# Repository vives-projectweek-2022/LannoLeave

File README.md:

# Lannooleaf

> VIVES Project Week 2022

## Project overview

<!-- bijwerken -->

* Connectable 3D-printed leaves
* PCB-design with LEDs & communications
* Use an OTS or own communication protocol
* Webpage
* Control of leds

## [Hardware](./hardware)

### [Shape](./hardware/shape/)

Dit is onze shape. Een primitive unit met 8 leafs.

### [PCB](./hardware/pcb/)

<!-- afbeelding hardware -->

Iedere PCB bevat elk 16 RGB LED's en beschikken ieder over een eigen Raspberry Pi Pico en spanningsomzetter. De volledige documentatie over de hardware kan men [hier](./hardware/pcb/README.md) terugvinden.

## [Firmware](./firmware)

<!-- Joey, afbeelding Pico? -->

<!-- aanvullen -->

De firmware documentatie wordt automatisch gegenereed tijdens het build procces van de firmware. Deze is te vinden in de [firmware](./firmware/) folder waar het build procces word uitgelegd.

## [Software](./software/)

The [API](./software/api) connect with the SPI interface and communicates with the frontend, artnet and has a socket to run python processed gifs.

The [ArtNet](./software/artnet) api reicieves artnet broadcast messages ans sends them trough the websochet of the api to controll all the leds. The api mapps them depending on the coords.

The [Frontend](./software/frontend) from Jay is the webinterface and all of its files.

## Credits

### Team Members

* [Arno Schoutteten](https://github.com/madness007)
* [Jens Vanhove](https://github.com/JensVA)
* [Joey De Smet](https://github.com/JoeyDeSmet)
* [Jay D'Hulster](https://github.com/JayDHulster)

### Mentors

* [Nico De Witte](https://github.com/BioBoost)
* [Piet Cordemans](https://github.com/pcordemans)
* [Sille Van Landschoot](https://github.com/sillevl)
* [Jonas Lannoo](https://github.com/JonasLannoo)

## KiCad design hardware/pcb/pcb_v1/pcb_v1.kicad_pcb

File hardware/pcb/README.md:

# PCB Lannooleaf

## Schematic

## PCB (leaf)

| Front | Back |
|---|---|
|  |  |

## PCB (verbindingsstuk)

| Front | Back |
|---|---|
|  |  |

## Eigenschappen voedingsschakeling (LM2596)

* Bereik ingangsspanning: 4,5 - 40V (wij gebruiken 24V)
* Maximale uitgangsstroom: 3A

We hebben 16 RGB LED's die theoretisch maximaal 50mA nodig hebben. Samen met de pico die maximaal 100mA verbruikt komt dit neer op een totale stroom van `900mA` (op 5V) per leaf wat neerkomt op een `vermogen van 4,5W`. De stroom aan de 24V-kant is natuurlijk een stuk minder en bedraagt `190mA`. Het verlagen van de stroom tussen de leafs was de reden van het gebruiken van een spanningsomzetter per leaf.

## Aansluiten leafs

Om de leafs met elkaar te verbinden moeten de verbindingsstukken met hun male headers geklikt worden in de female headers van de leafs (female headers kant van Pico). Op onderstaande afbeelding kan men de functie van iedere pin zien op de leaf.

De buitenste 2 pinnen zijn voor het doorkoppelen van de voeding (24V en GND) tussen de leafs. De pinnen in het midden zijn beide dezelfde 'select' pin die dient voor het discovery-protocol. De overige pinnen dienen voor het doorkoppelen van de I²C-bus met SDA aan de binnenkant en SCL aan de buitenkant.

Let op dat je de spanning niet omgekeerd aansluit bij het eventueel rechtstreeks voeden van de leafs aan de headers omdat er `GEEN polariteitsbeveiliging` aanwezig is op deze versie van de PCB. Het is veiliger om de PCB's te voeden door gebruik te maken van de barrel-jack connector die men kan solderen op de voorziene plaats op de PCB.

## BOM (Bill of Materials)

| Designator | Quantity | Description | Footprint | Distributor | Ordercode | Price |
|---|---|---|---|---|---|---|
| U1 | 1 | Raspberry Pi Pico  | 2.54mm (2x20) | Farnell | [3643332](https://be.farnell.com/raspberry-pi/raspberry-pi-pico/raspberry-pi-32bit-arm-cortex/dp/3643332) | 3,27 € (1+) |
| | 2 | Headers pico  | 2.54mm (1x20) | TME | [ZL201-20G](https://www.tme.eu/be/nl/details/zl201-20g/lijsten-en-pin-achtige-stopcontacten/connfly/ds1021-1-20sf11/) | 0,17267  € (10+) |
| U2 | 1 | LM2575-05 (ADJ) | TO-263-5 | Farnell | [2534162](https://be.farnell.com/on-semiconductor/lm2596dsadjg/dc-dc-conv-buck-3a-150khz-to-263/dp/2534162) | 2,65 € (10+) |
| D1 - D16 | 16 | WS2812B addressable LEDS | 5050 | TME | [WS2812B-V5](https://www.tme.eu/be/nl/details/ws2812b-v5/led-diodes-smd-gekleurd/worldsemi/) | 0,1490 € (50+) |
| C1 - C16, C18, C23| 18 | 100nF | 0805 | Farnell | [2320821](https://be.farnell.com/multicomp/mc0805b104k101ct/cap-0-1-f-100v-10-x7r-0805/dp/2320821) | 0,048 € (250+) |
| C17, C22 | 2 | 1nF | 0805 | Farnell | [3019871](https://be.farnell.com/yageo/cc0805krx7r9bb102/cap-1000pf-50v-10-x7r-0805/dp/3019871) | 0,077 € (10+) |
| C19, C24 | 2 | 1µF | 0805 | Farnell | [3013482](https://be.farnell.com/samsung-electro-mechanics/cl21b105kbfnnne/cap-1uf-50v-mlcc-0805/dp/3013482) | 0,052 € (5+) |
| C20 | 1 | 100µF | 6,3x7,7mm | Farnell | [2611381](https://be.farnell.com/multicomp/mcvvt035m101ea6l/cap-100-f-35v-smd/dp/2611381) | 0,156 € (1+) |
| C21 | 1 | 220µF | 8x10,5mm | Farnell | [2611361](https://be.farnell.com/multicomp/mcvvt016m221fb3l/cap-220-f-16v-smd/dp/2611361) | 0,22 € (10+) |
| D17 | 1 | SS34 | DO-214AC (SMA) | Farnell | [2101195](https://be.farnell.com/multicomp/ss34a/diode-rectifier-3a-40v-do-214ac/dp/2101195) | 0,293 € (10+) |
| L1 | 1 | 33µH | 12x12x8mm | Farnell | [2288506](https://be.farnell.com/coilcraft/mss1278-333mld/inductor-33uh-3-1a-20-pwr-9-5mhz/dp/2288506) | 1,82 € (10+) |
| R1 | 1 | 3,1k | 0805 | Farnell | [2502845](https://be.farnell.com/walsin/wf08w3091btl/res-3k09-0-1-100v-0805-thin-film/dp/2502845) | 0,112 € (10+) |
| R2 | 1 | 1k | 0805 | Farnell | [2502859](https://be.farnell.com/walsin/wf08u1001btl/res-1k-0-1-100v-0805-thin-film/dp/2502859) | 0,103 € (10+) |
| J1-J6 | 6 | Pin sockets (2x5) | 2.54mm | TME | [ZL262-10DG](https://www.tme.eu/be/nl/details/zl262-10dg/lijsten-en-pin-achtige-stopcontacten/connfly/ds1023-2-5s21/) | 0,08281 € (100+) |

Volgende items zijn enkel voor de `controller` (leaf met speciale functionaliteit):

| Designator | Quantity | Description | Footprint | Distributor | Ordercode | Price |
|---|---|---|---|---|---|---|
| J7 | 1 | Power connector | | TME | [PC-GK2.5/SMD](https://www.tme.eu/be/en/details/pc-gk2.5_smd/dc-power-connectors/ninigi/) | 0,9084 € (2+) |
| J8 | 1 | Pin headers (1x5) right angle | 2.54mm | Farnell | [2356179](https://be.farnell.com/wurth-elektronik/61300511021/header-2-54mm-pin-tht-r-a-5way/dp/2356179) | 0,315 € (10+) |

Volgend item is enkel voor de `verbindingsstukken` tussen de leafs:

| Designator | Quantity | Description | Footprint | Distributor | Ordercode | Price |
|---|---|---|---|---|---|---|
| J1, J2 | 2 | Pin headers (2x5) | 2.54mm | TME | [ZL202-10G](https://www.tme.eu/be/nl/details/zl202-10g/lijsten-en-pin-achtige-stopcontacten/connfly/ds1021-2-5sf11-b/) | 0.05254 € (50+) |

Totale prijs componenten leaf: `12,9722 €`

Totale prijs componenten controller: `14,1956 €`

Totale prijs componenten verbindingsstuk: `0,10508 €`

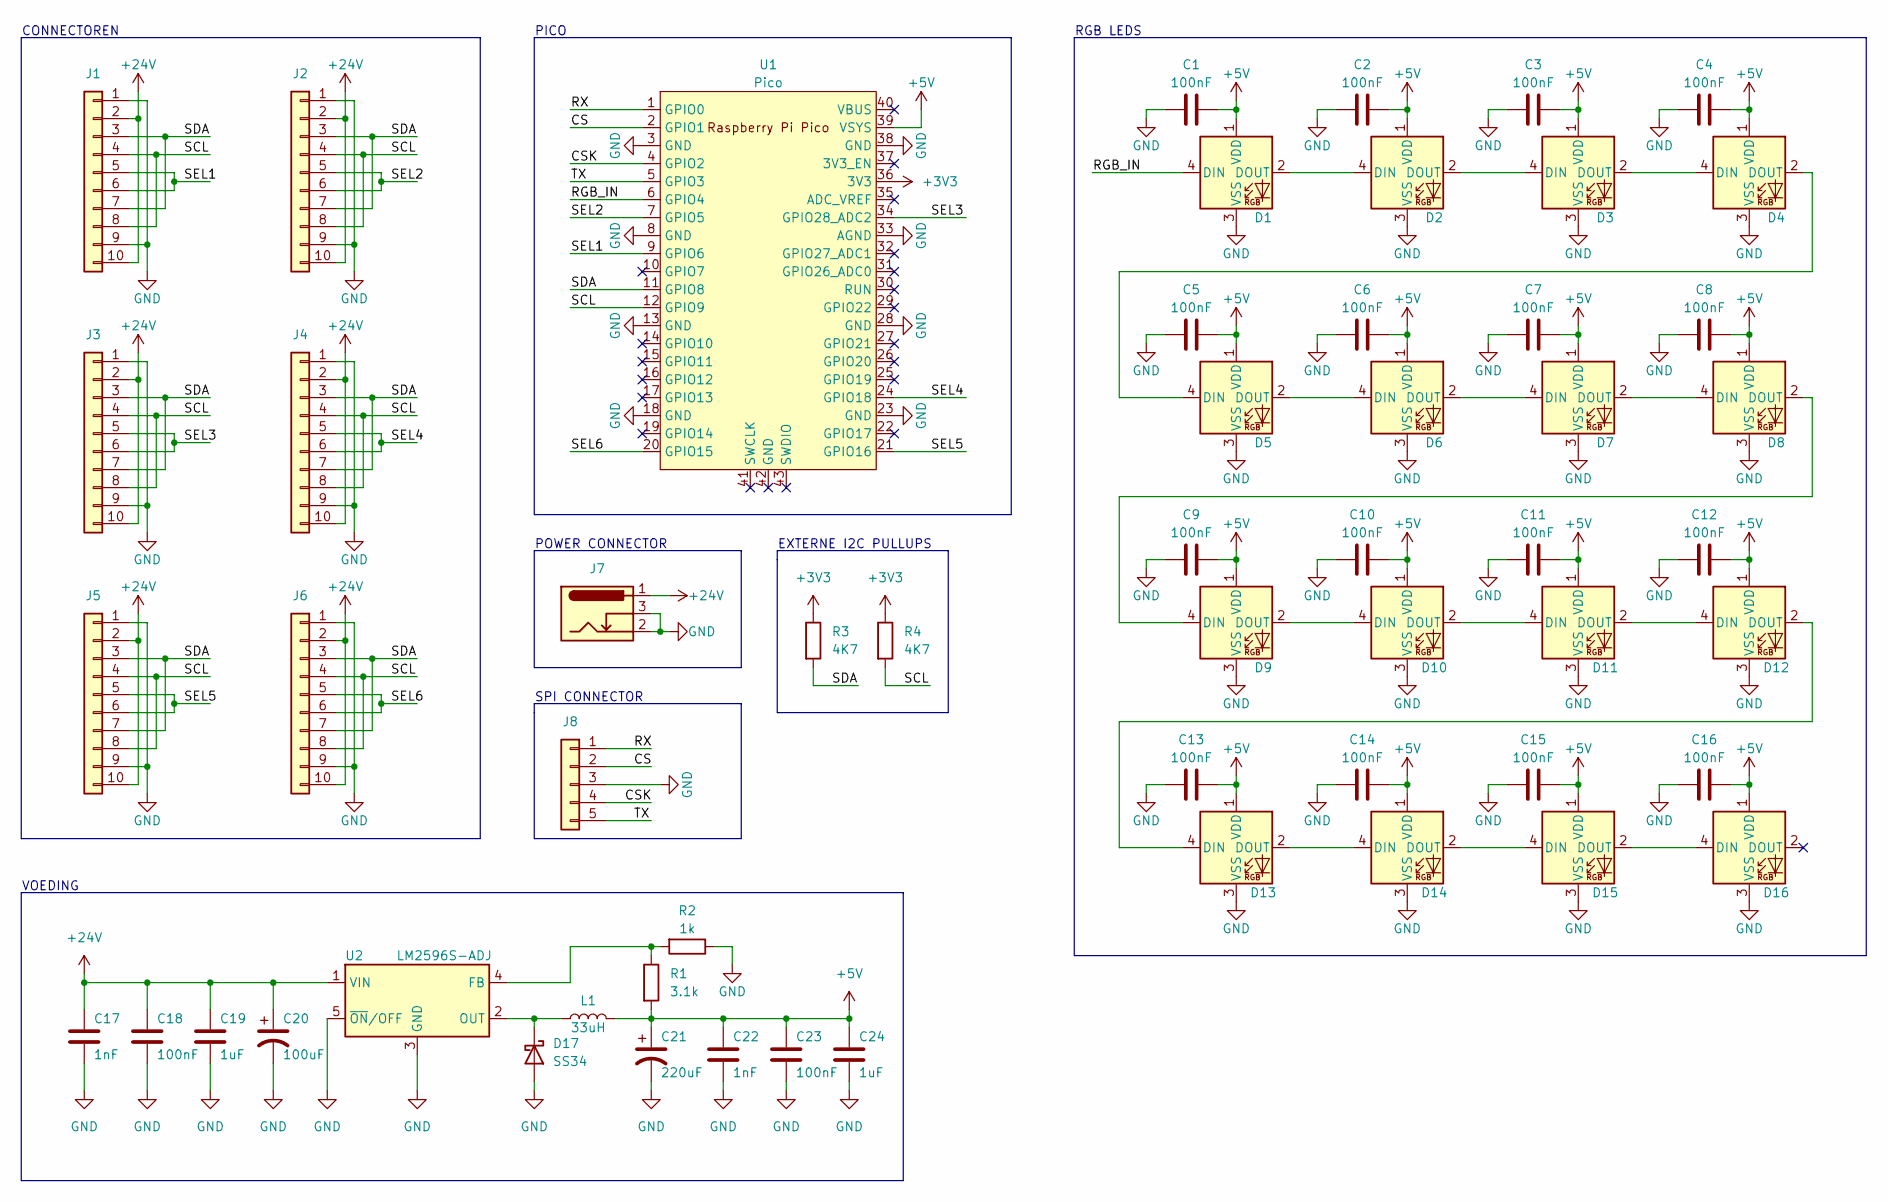
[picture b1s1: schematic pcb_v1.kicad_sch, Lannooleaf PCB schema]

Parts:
C1, C2, C3, C4, C5, C6, C7, C8, C9, C10, C11, C12, C13, C14, C15, C16, C18, C23: 100nF; C_0805_2012Metric
C17, C22: 1nF; C_0805_2012Metric
C19, C24: 1uF; C_0805_2012Metric
C20: 100uF; CP_Elec_6.3x7.7
C21: 220uF; CP_Elec_8x10.5
D1, D2, D3, D4, D5, D6, D7, D8, D9, D10, D11, D12, D13, D14, D15, D16: WS2812B; LED_WS2812B_PLCC4_5.0x5.0mm_P3.2mm
D17: SS34; D_SMA_Handsoldering
J1, J2, J3, J4, J5, J6: Conn_01x10; PinHeader_2x05_P2.54mm_Vertical
J7: Barrel_Jack_Switch; BarrelJack_CLIFF_FC681465S_SMT_Horizontal
J8: Conn_01x05; PinSocket_1x05_P2.54mm_Horizontal
L1: 33uH; L_12x12mm_H8mm
R1: 3.1k; R_0805_2012Metric
R2: 1k; R_0805_2012Metric
R3, R4: 4K7; R_0805_2012Metric
U1: Pico; RPi_Pico_SMD_TH
U2: LM2596S-ADJ; TO-263-5_TabPin3

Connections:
+3V3: R3.1, R4.1, U1.36 (3V3)
+5V: C1.2, C2.2, C3.2, C4.2, C5.2, C6.2, C7.2, C8.2, C9.2, C10.2, C11.2, C12.2, C13.2, C14.2, C15.2, C16.2, C21.1, C22.1, C23.1, C24.1, D1.1 (VDD), D2.1 (VDD), D3.1 (VDD), D4.1 (VDD), D5.1 (VDD), D6.1 (VDD), D7.1 (VDD), D8.1 (VDD), D9.1 (VDD), D10.1 (VDD), D11.1 (VDD), D12.1 (VDD), D13.1 (VDD), D14.1 (VDD), D15.1 (VDD), D16.1 (VDD), L1.2, R1.2, U1.39 (VSYS)
+24V: C17.1, C18.1, C19.1, C20.1, J1.2, J1.10, J2.2, J2.10, J3.2, J3.10, J4.2, J4.10, J5.2, J5.10, J6.2, J6.10, J7.1, U2.1 (VIN)
/CS: J8.2, U1.2 (GPIO1)
/CSK: J8.4, U1.4 (GPIO2)
/RGB_IN: D1.4 (DIN), U1.6 (GPIO4)
/RX: J8.1, U1.1 (GPIO0)
/SCL: J1.4, J1.8, J2.4, J2.8, J3.4, J3.8, J4.4, J4.8, J5.4, J5.8, J6.4, J6.8, R4.2, U1.12 (GPIO9)
/SDA: J1.3, J1.7, J2.3, J2.7, J3.3, J3.7, J4.3, J4.7, J5.3, J5.7, J6.3, J6.7, R3.2, U1.11 (GPIO8)
/SEL1: J1.5, J1.6, U1.9 (GPIO6)
/SEL2: J2.5, J2.6, U1.7 (GPIO5)
/SEL3: J3.5, J3.6, U1.34 (GPIO28_ADC2)
/SEL4: J4.5, J4.6, U1.24 (GPIO18)
/SEL5: J5.5, J5.6, U1.21 (GPIO16)
/SEL6: J6.5, J6.6, U1.20 (GPIO15)
/TX: J8.5, U1.5 (GPIO3)
GND: C1.1, C2.1, C3.1, C4.1, C5.1, C6.1, C7.1, C8.1, C9.1, C10.1, C11.1, C12.1, C13.1, C14.1, C15.1, C16.1, C17.2, C18.2, C19.2, C20.2, C21.2, C22.2, C23.2, C24.2, D1.3 (VSS), D2.3 (VSS), D3.3 (VSS), D4.3 (VSS), D5.3 (VSS), D6.3 (VSS), D7.3 (VSS), D8.3 (VSS), D9.3 (VSS), D10.3 (VSS), D11.3 (VSS), D12.3 (VSS), D13.3 (VSS), D14.3 (VSS), D15.3 (VSS), D16.3 (VSS), D17.2 (A), J1.1, J1.9, J2.1, J2.9, J3.1, J3.9, J4.1, J4.9, J5.1, J5.9, J6.1, J6.9, J7.2, J7.3, J8.3, R2.1, U1.3 (GND), U1.8 (GND), U1.13 (GND), U1.18 (GND), U1.23 (GND), U1.28 (GND), U1.33 (AGND), U1.38 (GND), U2.3 (GND), U2.5 (~ON/OFF)
unnamed: D1.2 (DOUT), D2.4 (DIN)
unnamed: D2.2 (DOUT), D3.4 (DIN)
unnamed: D3.2 (DOUT), D4.4 (DIN)
unnamed: D4.2 (DOUT), D5.4 (DIN)
unnamed: D5.2 (DOUT), D6.4 (DIN)
unnamed: D6.2 (DOUT), D7.4 (DIN)
unnamed: D7.2 (DOUT), D8.4 (DIN)
unnamed: D8.2 (DOUT), D9.4 (DIN)
unnamed: D10.2 (DOUT), D11.4 (DIN)
unnamed: D9.2 (DOUT), D10.4 (DIN)
unnamed: D11.2 (DOUT), D12.4 (DIN)
unnamed: D12.2 (DOUT), D13.4 (DIN)
unnamed: D13.2 (DOUT), D14.4 (DIN)
unnamed: D14.2 (DOUT), D15.4 (DIN)
unnamed: D15.2 (DOUT), D16.4 (DIN)
unnamed: D17.1 (K), L1.1, U2.2 (OUT)
unnamed: R1.1, R2.2, U2.4 (FB)

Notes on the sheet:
POWER CONNECTOR
EXTERNE I2C PULLUPS
VOEDING
PICO
CONNECTOREN
SPI CONNECTOR
RGB LEDS

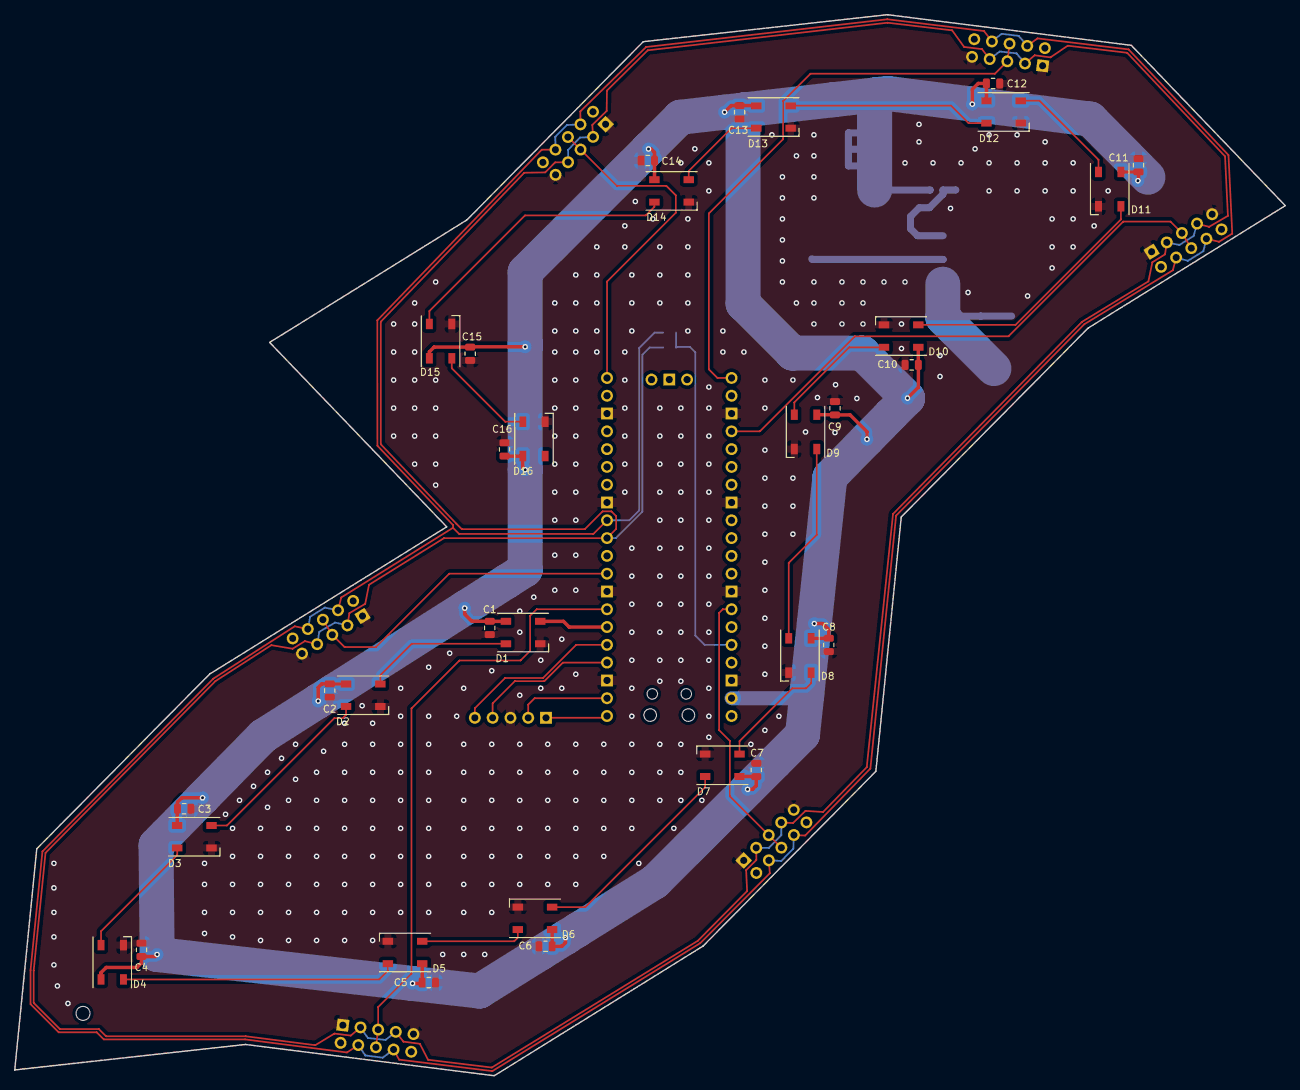
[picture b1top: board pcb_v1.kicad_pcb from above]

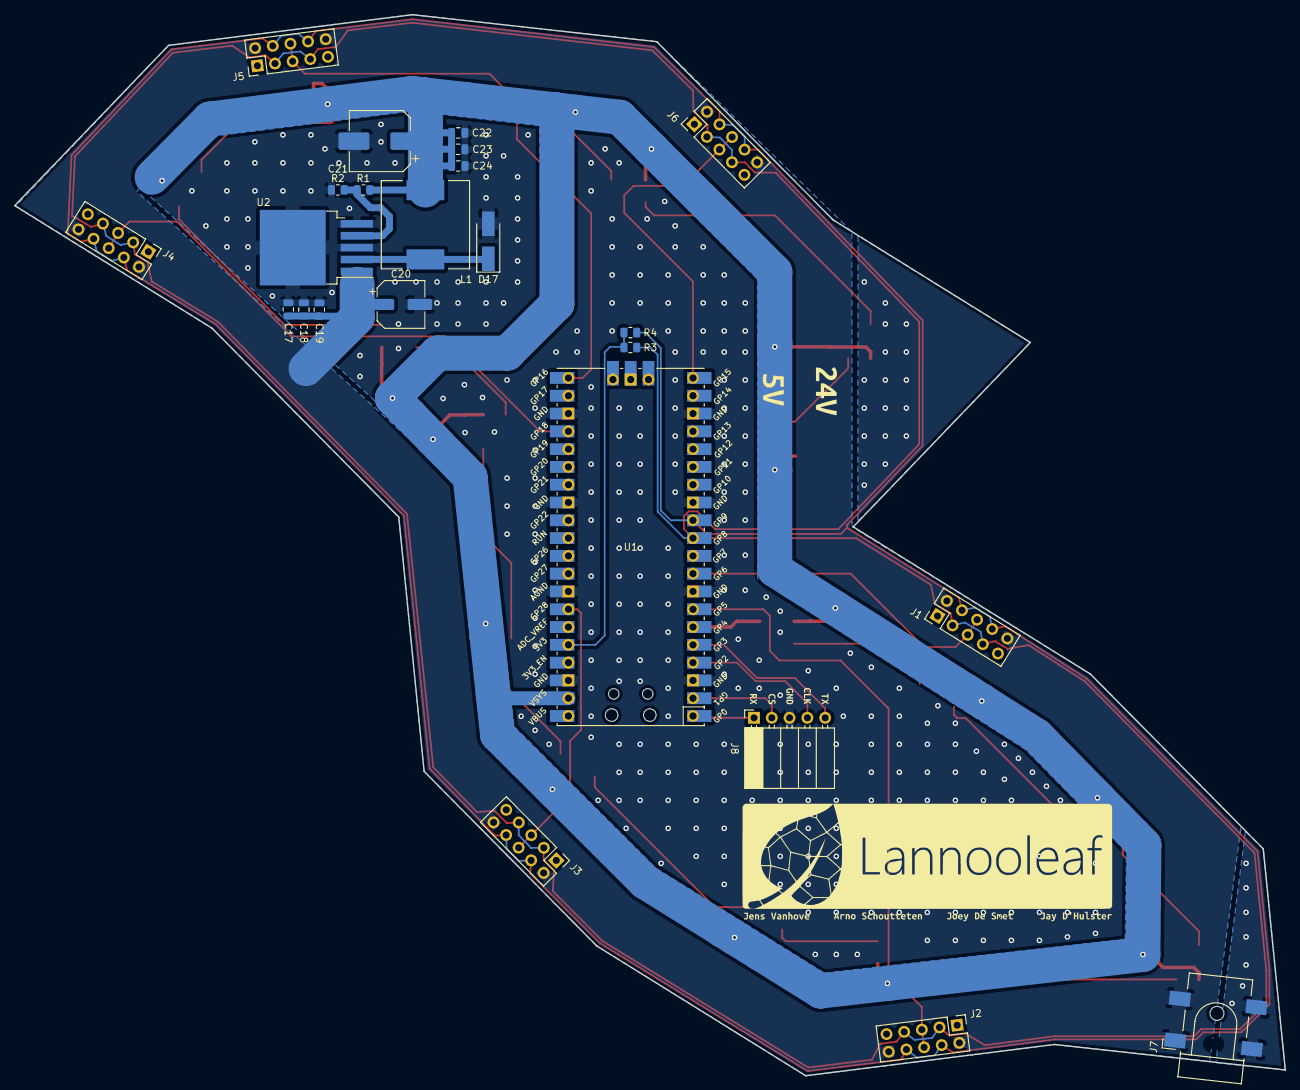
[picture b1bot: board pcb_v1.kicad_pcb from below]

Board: 2 copper layers, 181.4 x 151.5 mm, 67 parts (35 on the bottom side), 34 nets.

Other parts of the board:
kibuzzard-6233C5FE: G***; kibuzzard-6233C5FE
kibuzzard-6233C627: G***; kibuzzard-6233C627
kibuzzard-6233C655: G***; kibuzzard-6233C655
kibuzzard-6233C670: G***; kibuzzard-6233C670
kibuzzard-6234ACC3: G***; kibuzzard-6234ACC3
kibuzzard-6234ACD1: G***; kibuzzard-6234ACD1
kibuzzard-6234ACE5: G***; kibuzzard-6234ACE5
kibuzzard-6234ACFA: G***; kibuzzard-6234ACFA
kibuzzard-6234AD1C: G***; kibuzzard-6234AD1C
kibuzzard-6234B02F: G***; kibuzzard-6234B02F
kibuzzard-6234B014: G***; kibuzzard-6234B014

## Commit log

2022-02-18 strenghts
2022-02-18 Added interests
2022-02-18 arno
2022-02-18 strengths filled in
2022-02-18 Added changes
2022-02-18 merge
2022-02-18 taken verdeeld
2022-02-18 added logotje
2022-02-18 logo update
2022-02-20 tiler
2022-02-20 folders
2022-02-20 Added some software
2022-02-21 Updated Protocol readme
2022-02-21 sterktes / interesses
2022-02-22 photo
2022-02-22 Added start for pico_project
2022-02-22 Updated gitignore
2022-02-22 presentation
2022-02-23 commitje
2022-02-23 web interface
2022-02-23 Removed mbed test
2022-02-23 Added basic i²c communication & device detection
2022-02-23 Fixed typo
2022-02-23 leave shape
2022-02-23 Refactoring of code
2022-02-23 inline dxf
2022-02-23 inline fix
2022-02-23 updated pcbv1
2022-02-25 pcbv1 updated (MC34166 added)
2022-02-26 Added dynamic ic adressing and graph data structure
2022-03-05 Added topology algorithm and refactoring
2022-03-09 Optimized topology discovery
2022-03-09 Added picoled lib
2022-03-09 web-interface
2022-03-09 eeewojoooooooo videoooooooo :)
2022-03-09 Removed files
2022-03-09 new logo webinterface
2022-03-09 new logo
2022-03-09 TL2575-05 added
2022-03-11 worked on pcbv1
2022-03-13 finished pcbv1
2022-03-14 updated pcb
2022-03-15 colorleaf
2022-03-15 presentation2 added
2022-03-16 Fixed minor bug
2022-03-16 background webint
2022-03-16 Moved software to firmware
2022-03-16 software
2022-03-16 docker-compose
2022-03-16 Made some changes to uart command handeling
2022-03-16 icon and script
2022-03-16 Made branche
2022-03-17 made changes
2022-03-17 Added documentation
2022-03-18 typo
2022-03-20 pcb updated
2022-03-21 aliexpress BOM
2022-03-21 modified pcb
2022-03-22 Added spi communication
2022-03-22 Removed spi branch
2022-03-22 Ignoring doxygen generated files
2022-03-22 added javascript for communication over spi with controller
2022-03-23 frontend
2022-03-23 merge...
2022-03-23 npm install
2022-03-23 readme
2022-03-23 setup basic api
2022-03-23 javascriptje
2022-03-23 node routes added, also joey changes some things
2022-03-23 javascript
2022-03-23 added some more code :)
2022-03-25 removed old c style typdef enum to modern enum class
2022-03-25 readme typo
2022-03-25 Refactored Leaf class
2022-03-25 Refactored controller class
2022-03-26 Refactored rest of classes
2022-03-29 Made changes to spi_slave class an renamed namespace
2022-03-29 rip LannoLeave & Lannoo Leave
2022-03-30 better json
2022-03-30 shape fusion
2022-03-30 changes pcb
2022-03-30 websocket demo
2022-03-30 Removed pixelmapping
2022-03-30 jquery
2022-03-30 Removed bugs
2022-03-31 Redesigned Spi_slave class
2022-03-31 Redesigned I2c_master & multicore
2022-04-01 dropdown
2022-04-03 changes made
2022-04-11 Changed spi_slave
2022-04-12 Made changes to Spi and I2c slave, project now compiles to one singular file
2022-04-18 Refactoring & added Spi_controller to software
2022-04-18 added spicontroller
2022-04-19 presentation3 added
2022-04-20 change name leave to leaf
2022-04-20 node more word :)
2022-04-20 drop down menu
2022-04-20 completed dropdown
2022-04-20 copyright
2022-04-20 it works :)
2022-04-22 Adding changes
2022-04-29 Replaced std::queue with pico queue to be thread safe
2022-04-30 Added image mapping script
2022-05-03 cleanded up software folder
2022-05-03 added unit
2022-05-03 moved var and addd comment
2022-05-03 stuff
2022-05-03 api server
2022-05-03 artnet api
2022-05-04 artnet
2022-05-04 upload wip
2022-05-04 AUB arno
2022-05-04 post
2022-05-04 idk if this works
2022-05-04 Create LICENSE
2022-05-04 some more work
2022-05-05 repo cleanup
2022-05-05 Begin adding documentation
2022-05-05 Added readme to firmware
2022-05-05 Documented classes
2022-05-05 Renamed I2CSlave and SPISlave class
2022-05-06 wrong presentation
2022-05-06 Refactored api class & added websocket to dmx
2022-05-07 Added option to run client.py to run without interpolation
2022-05-10 Major changes to spi and i2c
2022-05-10 Adding changes from ri pi
2022-05-21 hardware documentation updated
2022-05-21 Adding local differences
